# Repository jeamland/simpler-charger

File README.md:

# A "Simpler"[^1] Charger

This is a two-port USB charger design based around the [Texas Instruments TPS25858-Q1](https://www.ti.com/product/TPS25858-Q1) controller. It's designed to be part of a larger project to build some charging infrastructure into a shelf, hence the terminal block connections rather than actual USB-C ports. Input power is intended to be 15V coming from a power brick and the intent is to have several of these providing something like 12 ports in total (so 6 completed boards).

A lot of the layout and component selection was "inspired" by [TI's Evaluation Kit](https://www.ti.com/tool/TPS25858Q1EVM-140) for this device, but I have deviated in a few places, mainly for cost reasons. I ~~hope~~think I've validated that these changes are ok.

Full KiCad files, including custom symbols and footprints, are in here along with datasheets, PDF versions of the schematic and PCB layout, and the bill of materials.

[^1]: The original design I made did the full USB-C thing up to 60W and required an actual microcontroller. I may still make that one but, well, I figured I should overcomplicate things in stages.

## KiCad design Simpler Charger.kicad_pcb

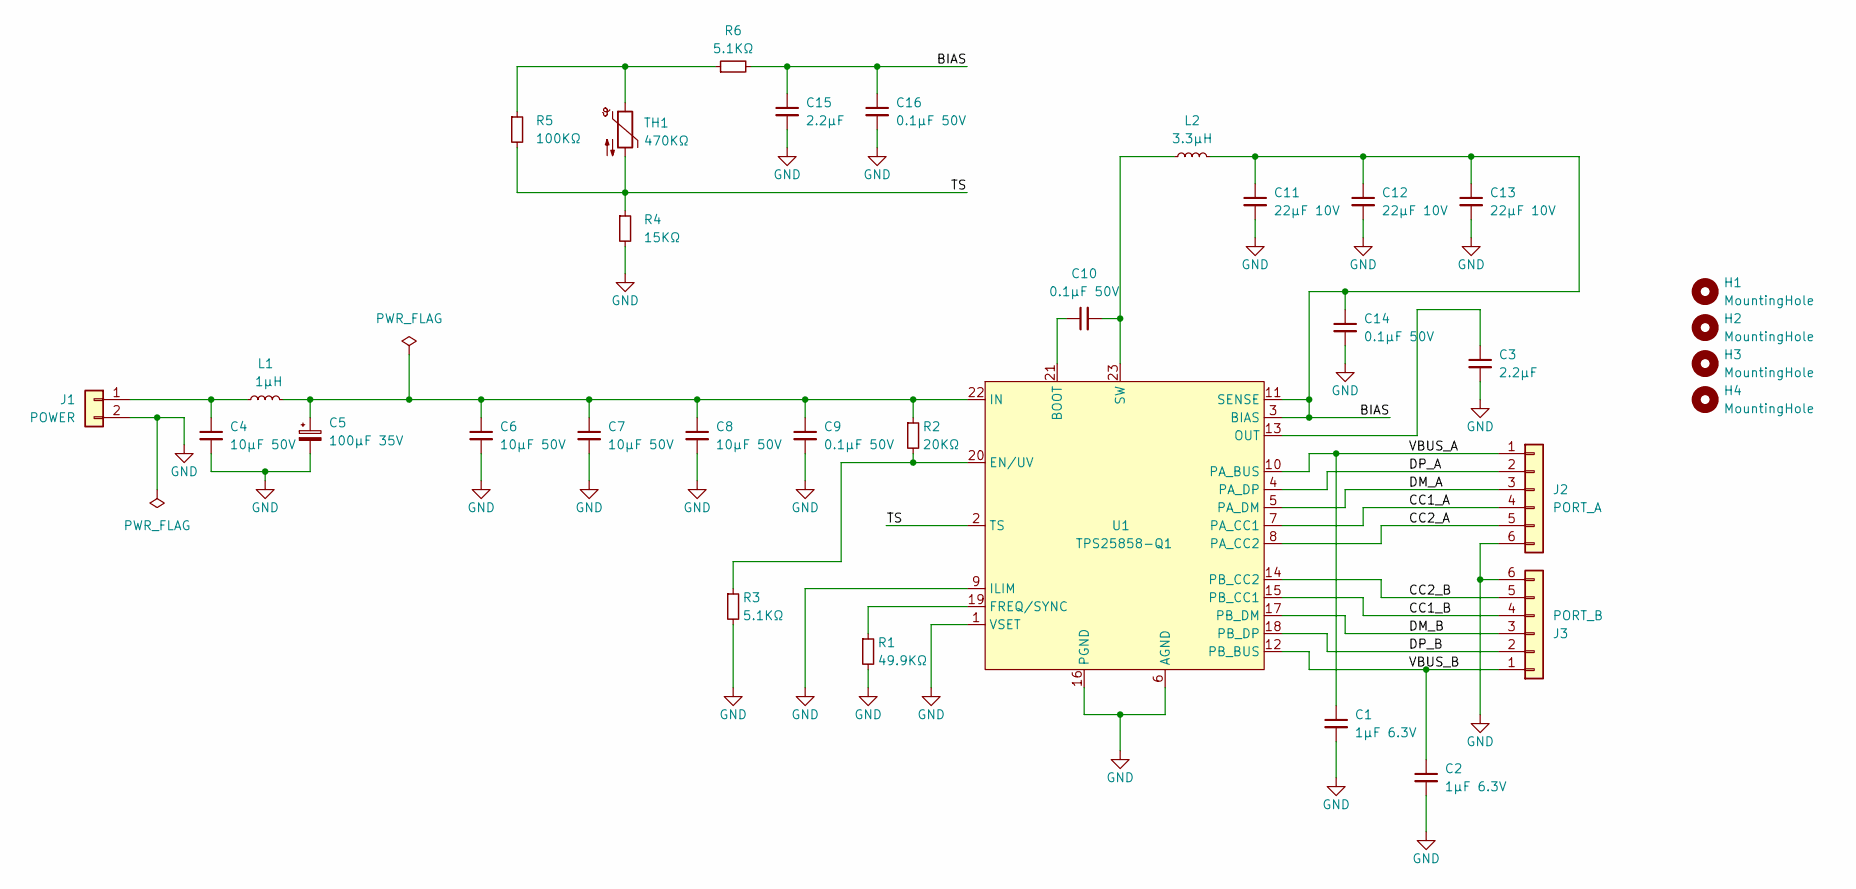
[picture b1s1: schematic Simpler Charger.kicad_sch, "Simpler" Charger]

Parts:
C1, C2: 1µF 6.3V; C_0603_1608Metric; Manufacturer Part No CL10B105KQ8NFNC
C3, C15: 2.2µF; C_0603_1608Metric; Manufacturer Part No KGM15AR51C225MT
C4: 10µF 50V; C_1210_3225Metric; Manufacturer Part No GRM32ER71H106MA12L
C5: 100µF 35V; CP_Radial_D6.3mm_P2.50mm; Manufacturer Part No 35ZLJ100M6.3X11
C6, C7, C8: 10µF 50V; C_1206_3216Metric; Manufacturer Part No GRT31CR61H106KE01L
C9: 0.1µF 50V; C_1206_3216Metric; Manufacturer Part No CL31B104KBCNFNC
C10, C14, C16: 0.1µF 50V; C_0603_1608Metric; Manufacturer Part No CL10B104KB8NFNC
C11, C12, C13: 22µF 10V; C_0805_2012Metric; Manufacturer Part No GRM21BZ71A226ME15L
H1, H2, H3, H4: MountingHole; MountingHole_3.2mm_M3_Pad_TopBottom
J1: POWER; TerminalBlock_Phoenix_PTSM-0,5-2-2.5-V-THR_1x02_P2.50mm_Ver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; Manufacturer Part No 1770953
J2: PORT_A; TerminalBlock_Phoenix_PTSM-0,5-6-2.5-V-THR_1x06_P2.50mm_Ver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; Manufacturer Part No 1770995
J3: PORT_B; TerminalBlock_Phoenix_PTSM-0,5-6-2.5-V-THR_1x06_P2.50mm_Ver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; Manufacturer Part No 1770995
L1: 1µH; BMRx00060630; Manufacturer Part No BMRA000606301R0MA1
L2: 3.3µH; L_Vishay_IHLP-5050; Manufacturer Part No IHLP5050FDER3R3M51
R1: 49.9KΩ; R_0603_1608Metric; Manufacturer Part No ERJ-3EKF4992V
R2: 20KΩ; R_0603_1608Metric; Manufacturer Part No CRCW060320K0JNEA
R3, R6: 5.1KΩ; R_0603_1608Metric; Manufacturer Part No CRCW06035K10JNEAC
R4: 15KΩ; R_0603_1608Metric; Manufacturer Part No RT0603DRE0715KL
R5: 100KΩ; R_0603_1608Metric; Manufacturer Part No CRCW0603100KFKEA
TH1: 470KΩ; R_0603_1608Metric; Manufacturer Part No NCP18WM474E03RB
U1: TPS25858-Q1; Manufacturer Part No TPS25858QRPQRQ1

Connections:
/BIAS: C11.1, C12.1, C13.1, C14.1, C15.1, C16.1, L2.2, R6.2, U1.3 (BIAS), U1.11 (SENSE)
/CC1_A: J2.4, U1.7 (PA_CC1)
/CC1_B: J3.4, U1.15 (PB_CC1)
/CC2_A: J2.5, U1.8 (PA_CC2)
/CC2_B: J3.5, U1.14 (PB_CC2)
/DM_A: J2.3, U1.5 (PA_DM)
/DM_B: J3.3, U1.17 (PB_DM)
/DP_A: J2.2, U1.4 (PA_DP)
/DP_B: J3.2, U1.18 (PB_DP)
/TS: R4.1, R5.2, TH1.2, U1.2 (TS)
/VBUS_A: C1.1, J2.1, U1.10 (PA_BUS)
/VBUS_B: C2.1, J3.1, U1.12 (PB_BUS)
GND: C1.2, C2.2, C3.2, C4.2, C5.2, C6.2, C7.2, C8.2, C9.2, C11.2, C12.2, C13.2, C14.2, C15.2, C16.2, J1.2, J2.6, J3.6, R1.2, R3.2, R4.2, U1.1 (VSET), U1.6 (AGND), U1.9 (ILIM), U1.16 (PGND), U1.24 (PGND), U1.25 (PGND)
unnamed: C4.1, J1.1, L1.1
unnamed: R5.1, R6.1, TH1.1
unnamed: C10.1, U1.21 (BOOT)
unnamed: R2.2, R3.1, U1.20 (EN/UV)
unnamed: R1.1, U1.19 (FREQ/SYNC)
unnamed: C5.1, C6.1, C7.1, C8.1, C9.1, L1.2, R2.1, U1.22 (IN)
unnamed: C3.1, U1.13 (OUT)
unnamed: C10.2, L2.1, U1.23 (SW)

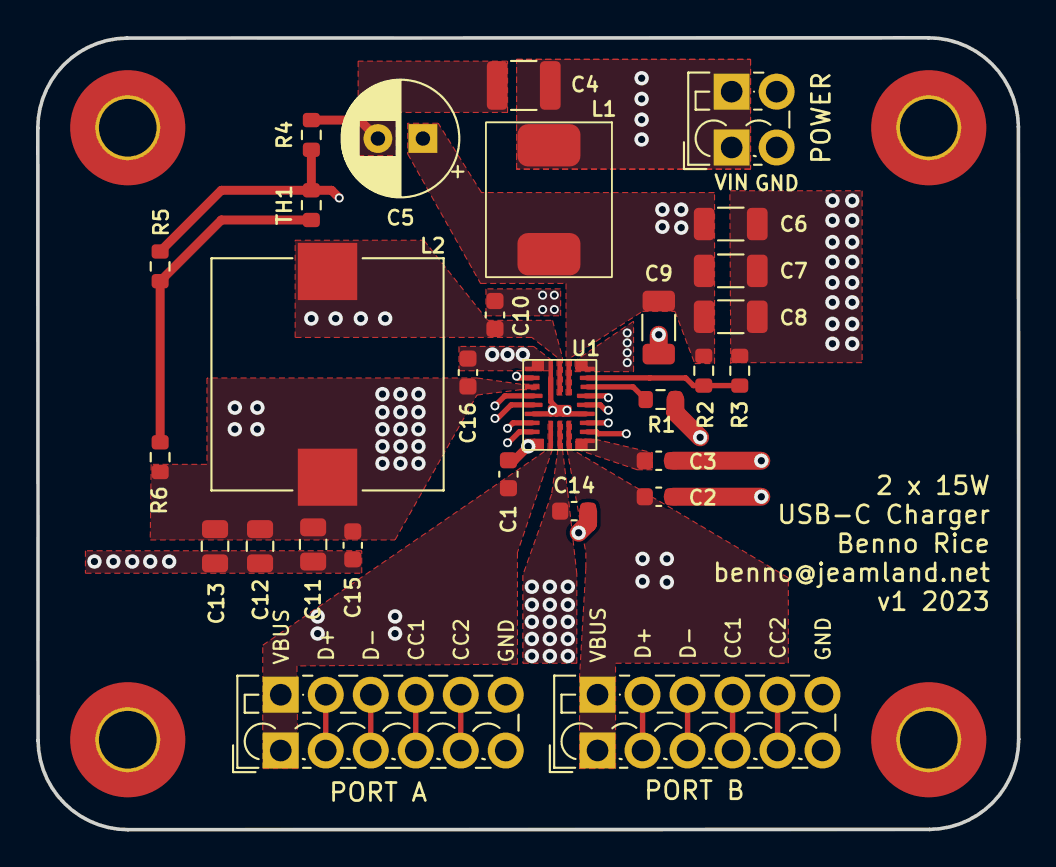
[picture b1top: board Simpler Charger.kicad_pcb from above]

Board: 4 copper layers, 54.5 x 44.0 mm, 33 parts (0 on the bottom side), 21 nets.

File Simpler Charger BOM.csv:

"Reference","Value","Description","Manufacturer","Manufacturer Part No","Qty"
"C1, C2","1µF 6.3V","CAP CER 1UF 6.3V X7R 0603","Samsung Electro-Mechanics","CL10B105KQ8NFNC","2"
"C3, C15","2.2µF","CAP CER 2.2UF 16V X5R 0603","Kyocera AVX","KGM15AR51C225MT","2"
"C4","10µF 50V","CAP CER 10UF 50V X7R 1210","Murata Electronics","GRM32ER71H106MA12L","1"
"C5","100µF 35V","CAP ALUM 100UF 20% 35V RADIAL","Rubycon","35ZLJ100M6.3X11","1"
"C6-C8","10µF 50V","CAP CER 10UF 50V X5R 1206","Murata Electronics","GRT31CR61H106KE01L","3"
"C9","0.1µF 50V","CAP CER 0.1UF 50V X7R 1206","Samsung Electro-Mechanics","CL31B104KBCNFNC","1"
"C10, C14, C16","0.1µF 50V","CAP CER 0.1UF 50V X7R 0603","Samsung Electro-Mechanics","CL10B104KB8NFNC","3"
"C11-C13","22µF 10V","CAP CER 22UF 10V X7R 0805","Murata Electronics","GRM21BZ71A226ME15L","3"
"J1","POWER","TERM BLK 2P TOP ENTRY 2.5MM PCB","Phoenix Contact","1770953","1"
"J2","PORT_A","TERM BLK 6P TOP ENTRY 2.5MM PCB","Phoenix Contact","1770995","1"
"J3","PORT_B","TERM BLK 6P TOP ENTRY 2.5MM PCB","Phoenix Contact","1770995","1"
"L1","1µH","FIXED IND 1UH 12A 10 MOHM SMD","Pulse Electronics","BMRA000606301R0MA1","1"
"L2","3.3µH","FIXED IND 3.3UH 20.2A 5.44 MOHM","Vishay Dale","IHLP5050FDER3R3M51","1"
"R1","49.9KΩ","RES SMD 49.9K OHM 1% 1/10W 0603","Panasonic Electronic Components","ERJ-3EKF4992V","1"
"R2","20KΩ","RES SMD 20K OHM 5% 1/10W 0603","Vishay Dale","CRCW060320K0JNEA","1"
"R3, R6","5.1KΩ","RES 5.1K OHM 5% 1/10W 0603","Vishay Dale","CRCW06035K10JNEAC","2"
"R4","15KΩ","RES SMD 15K OHM 0.5% 1/10W 0603","YAGEO","RT0603DRE0715KL","1"
"R5","100KΩ","RES SMD 100K OHM 1% 1/10W 0603","Vishay Dale","CRCW0603100KFKEA","1"
"TH1","470KΩ","THERM NTC 470KOHM 4500K 0603","Murata Electronics","NCP18WM474E03RB","1"
"U1","TPS25858-Q1","Dual 3A USB Type-C Charging Ports Controller with Programmable Current Limit and Thermal Management, RPQ0025A (VQFN-25)","Texas Instruments","TPS25858QRPQRQ1","1"

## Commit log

2023-11-07 KiCad files
2023-11-07 .gitignore
2023-11-07 Schematic PDF
2023-11-07 PCB PDF (one layer per page)
2023-11-07 Datasheets
2023-11-07 Add LICENSE
2023-11-07 Readme
2023-11-07 Forgot to mark up a gag
2023-11-07 Move things around so L2's loop is shorter
2023-11-08 Hopefully better thermals for the high-current bits
2023-11-09 Adjust silkscreen text sizes, put mounting holes in paste layer
2023-11-10 Round corners, shuffle some silkscreens
2023-11-10 No idea.
